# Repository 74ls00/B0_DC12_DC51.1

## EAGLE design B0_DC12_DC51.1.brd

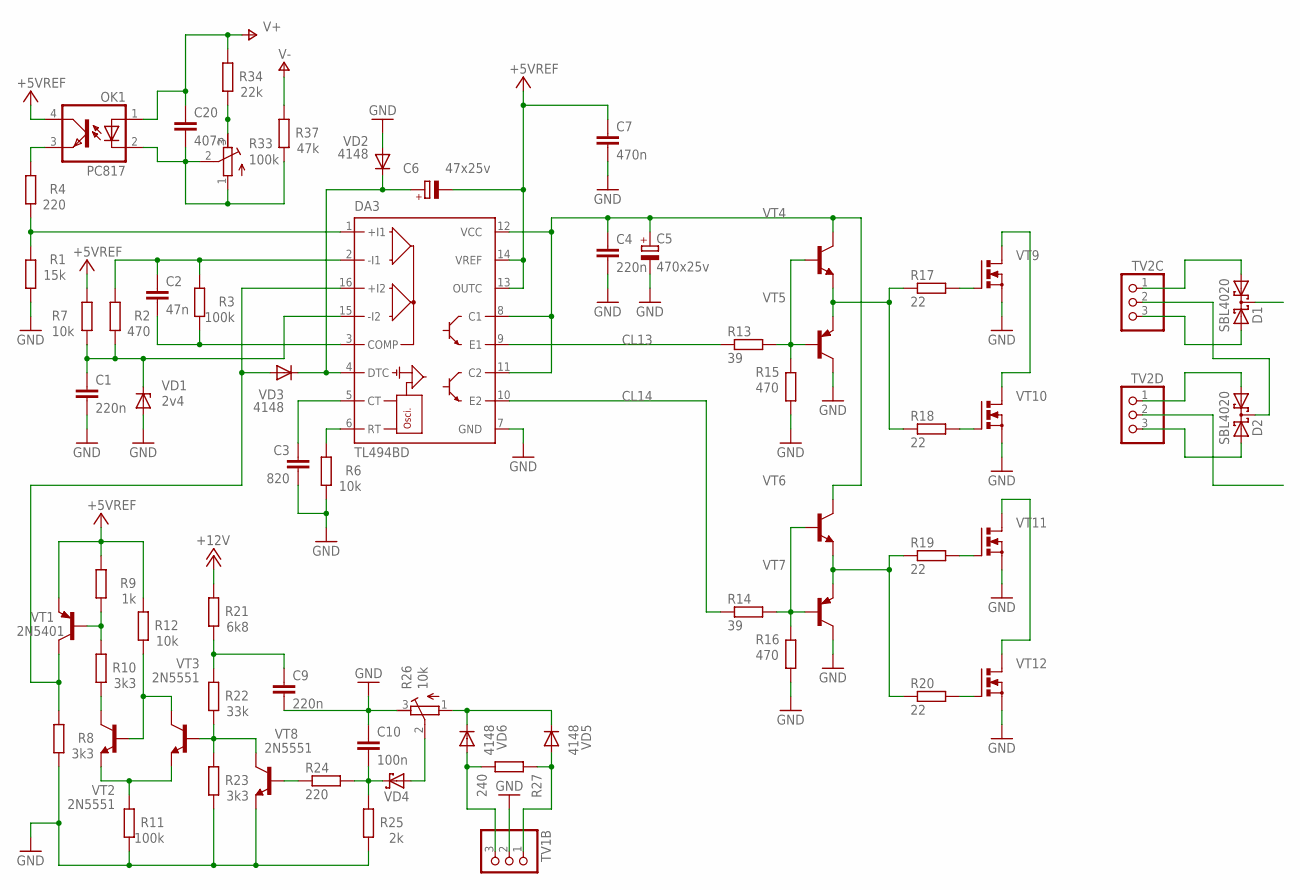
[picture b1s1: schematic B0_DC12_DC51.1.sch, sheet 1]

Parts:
C1, C4, C9: 220n; C0805
C2: 47n; C0805
C3: 820; C025-025X050
C5: 470x25v; E5-10,5
C6: 47x25v; E5-10,5
C7: 470n; C0805
C10: 100n; C0805
C20: 407n; C0805
D1, D2: SBL4020; TO247H
DA3: TL494BD; SO16
OK1: PC817; DIL04
R1: 15k; M0805
R2, R15, R16: 470; M0805
R3: 100k; R0805
R4, R24: 220; M0805
R6: 10k; 0207/12
R7, R12: 10k; M0805
R8, R10, R23: 3k3; M0805
R9: 1k; M0805
R11: 100k; M0805
R13, R14: 39; M0805
R17, R18, R19, R20: 22; M0805
R21: 6k8; M0805
R22: 33k; M0805
R25: 2k; M0805
R26: 10k; RTRIM3296W
R27: 240; 0207/10
R33: 100k; RTRIM3296W
R34: 22k; M0805
R37: 47k; M0805
TV1B, TV2C, TV2D: PINHD-1X3; 1X03
VD1: 2v4; SOD80C
VD2, VD3, VD5, VD6: 4148; SOD80C
VD4: 1N5817-B; DO41-7.6
VT1: 2N5401; TO92
VT2, VT3, VT8: 2N5551; TO92
VT4, VT6: -NPN-TO126V; TO126V
VT5, VT7: -PNP-TO126V; TO126V
VT9, VT10, VT11, VT12: MOSFET-N_DPACK; DPACK

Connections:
+5VREF: C6.-, C7.1, DA3.13 (OUTC), DA3.14 (VREF), OK1.4 (COL), R7.2, R9.2, R12.2, VT1.1 (E)
+12V: R21.2
CL13: DA3.9 (E1), R13.1
CL14: DA3.10 (E2), R14.1
GND: C1.2, C3.2, C4.2, C5.-, C7.2, C9.2, C10.1, DA3.7 (GND), R1.1, R6.1, R8.1, R11.1, R15.1, R16.1, R23.1, R25.1, R26.3 (E), TV1B.2, VD1.A, VD2.A, VT5.2 (C), VT7.2 (C), VT8.1 (E), VT9.S, VT10.S, VT11.S, VT12.S
unnamed: DA3.6 (RT), R6.2
unnamed: C3.1, DA3.5 (CT)
unnamed: VT9.D, VT10.D
unnamed: R17.2, VT9.G
unnamed: R18.2, VT10.G
unnamed: C2.2, DA3.3 (COMP), R3.1
unnamed: C1.1, DA3.15 (-I2), R2.1, R7.1, VD1.C
unnamed: R13.2, R15.2, VT4.3 (B), VT5.3 (B)
unnamed: R17.1, R18.1, VT4.1 (E), VT5.1 (E)
unnamed: R14.2, R16.2, VT6.3 (B), VT7.3 (B)
unnamed: R19.1, R20.1, VT6.1 (E), VT7.1 (E)
unnamed: VT11.D, VT12.D
unnamed: DA3.16 (+I2), R8.2, VD3.A, VT1.2 (C)
unnamed: OK1.3 (EMIT), R4.2
unnamed: C4.1, C5.+, DA3.8 (C1), DA3.11 (C2), DA3.12 (VCC), VT4.2 (C), VT6.2 (C)
unnamed: R27.2, TV1B.1, VD5.A
unnamed: R19.2, VT11.G
unnamed: R20.2, VT12.G
unnamed: DA3.1 (+I1), R1.2, R4.1
unnamed: C6.+, DA3.4 (DTC), VD2.C, VD3.C
unnamed: C20.2, OK1.2 (C), R33.1 (A), R33.2 (S), R37.1
unnamed: C2.1, DA3.2 (-I1), R2.2, R3.2
unnamed: R9.1, R10.2, VT1.3 (B)
unnamed: R33.3 (E), R34.1
unnamed: R27.1, TV1B.3, VD6.A
unnamed: R10.1, VT2.2 (C)
unnamed: R12.1, VT2.3 (B), VT3.2 (C)
unnamed: R11.2, VT2.1 (E), VT3.1 (E)
unnamed: R22.1, R23.2, VT3.3 (B), VT8.2 (C)
unnamed: C9.1, R21.1, R22.2
unnamed: R24.1, VT8.3 (B)
unnamed: C10.2, R24.2, R25.2, VD4.C
unnamed: R26.2 (S), VD4.A
unnamed: R26.1 (A), VD5.C, VD6.C
unnamed: D1.1 (A1), TV2C.1
unnamed: D1.3 (A2), TV2C.3
unnamed: D2.1 (A1), TV2D.1
unnamed: D2.3 (A2), TV2D.3
unnamed: D2.2 (C), TV2C.2
V+: C20.1, OK1.1 (A), R34.2
V-: R37.2

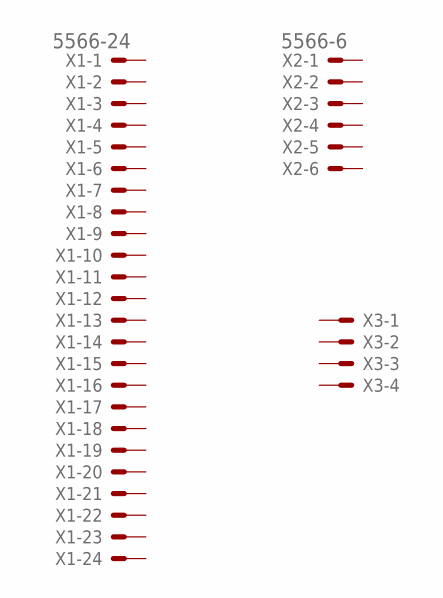
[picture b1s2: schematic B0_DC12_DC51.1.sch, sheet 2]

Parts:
X1: 5566-24
X2: 5566-6
X3: KK-156-4

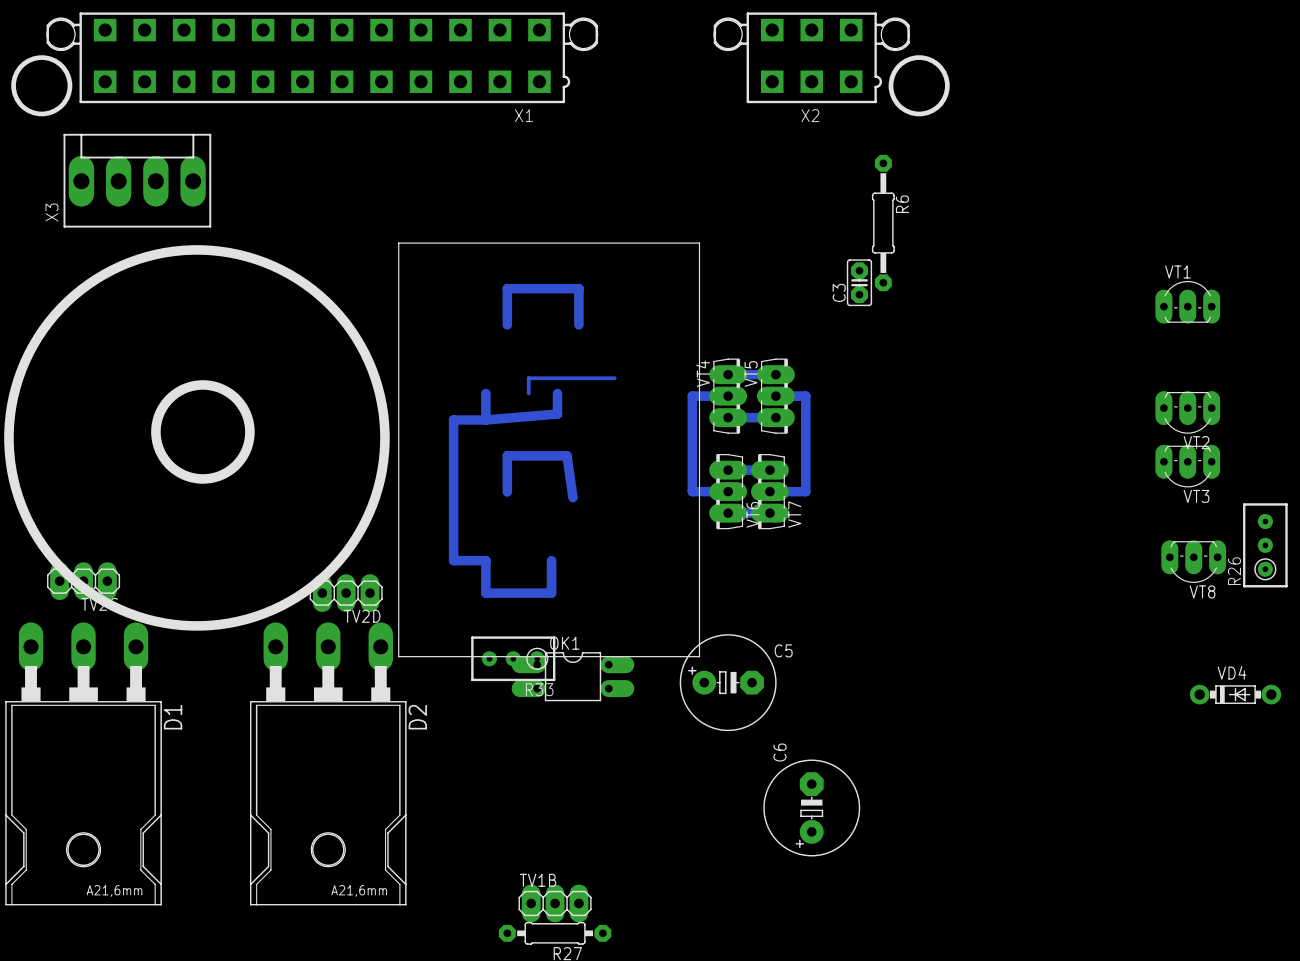
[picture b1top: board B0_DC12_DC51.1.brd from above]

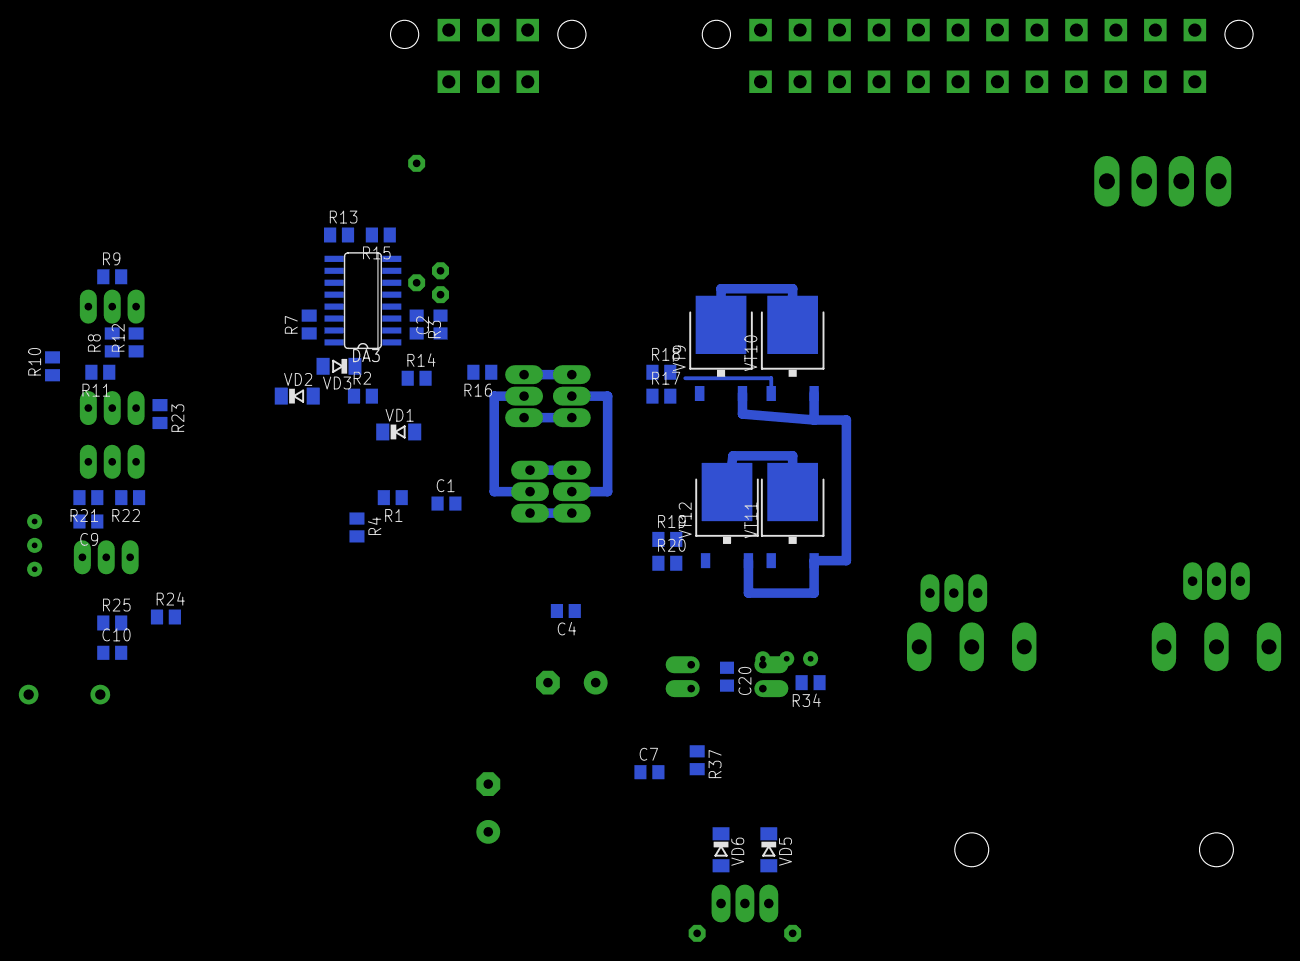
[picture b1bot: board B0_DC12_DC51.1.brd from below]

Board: 2 copper layers, 68 parts (42 on the bottom side), 44 nets.

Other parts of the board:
U$1: H44X32
